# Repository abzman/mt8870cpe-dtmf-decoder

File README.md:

# mt8870cpe-dtmf-decoder

https://abzman2k.wordpress.com/2024/01/01/dtmf-decoder-board-mitel-mt8870ce/

https://abzman2k.wordpress.com/2024/03/23/dtmf-decoder-board-testing-success/

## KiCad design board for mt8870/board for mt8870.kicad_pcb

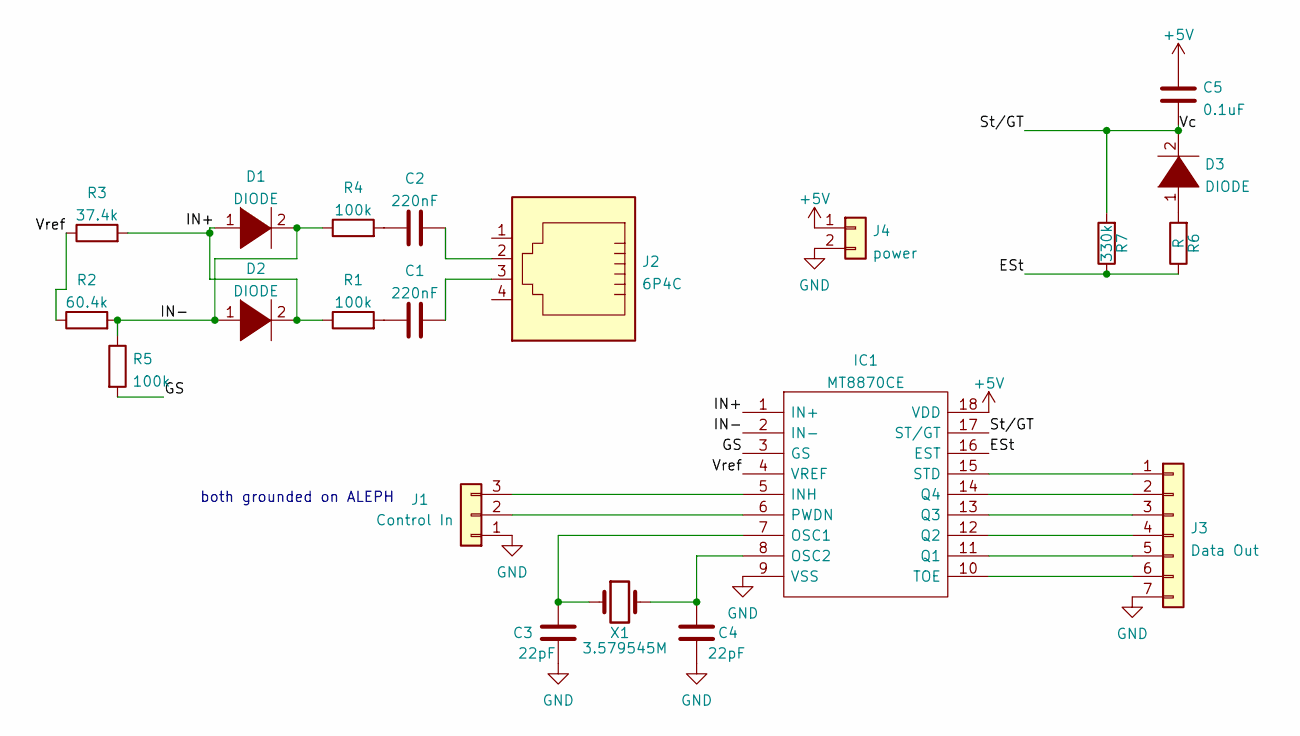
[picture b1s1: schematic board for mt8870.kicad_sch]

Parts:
C1, C2: 220nF; C_Rect_L7.0mm_W3.5mm_P5.00mm
C3, C4: 22pF; C_0603_1608Metric
C5: 0.1uF; C_0603_1608Metric
D1, D2, D3: DIODE; D_A-405_P5.08mm_Vertical_AnodeUp
IC1: MT8870CE; DIP-18_W7.62mm; Manufacturer_Part_Number MT8870CE
J1: Control In; PinHeader_1x03_P2.54mm_Vertical
J2: 6P4C; RJ14_Connfly_DS1133-S4_Horizontal
J3: Data Out; PinHeader_1x07_P2.54mm_Vertical
J4: power; PinHeader_1x02_P2.54mm_Vertical
R1, R4, R5: 100k; R_Axial_DIN0207_L6.3mm_D2.5mm_P5.08mm_Vertical
R2: 60.4k; R_Axial_DIN0207_L6.3mm_D2.5mm_P5.08mm_Vertical
R3: 37.4k; R_Axial_DIN0207_L6.3mm_D2.5mm_P5.08mm_Vertical
R6: R; R_Axial_DIN0207_L6.3mm_D2.5mm_P5.08mm_Vertical
R7: 330k; R_Axial_DIN0207_L6.3mm_D2.5mm_P5.08mm_Vertical
X1: 3.579545M; Crystal_HC49-U_Vertical

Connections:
+5V: C5.1, IC1.18 (VDD), J4.1
/ESt: IC1.16 (EST), R6.1, R7.1
/GS: IC1.3 (GS), R5.2
/IN+: D1.1 (K), D2.2 (A), IC1.1 (IN+), R1.1, R3.2
/IN-: D1.2 (A), D2.1 (K), IC1.2 (IN-), R2.2, R4.1, R5.1
/St/GT: C5.2, D3.2 (A), IC1.17 (ST/GT), R7.2
/Vref: IC1.4 (VREF), R2.1, R3.1
GND: C3.2, C4.2, IC1.9 (VSS), J1.1, J3.7, J4.2
unnamed: C1.2, J2.3
unnamed: C2.2, J2.2
unnamed: D3.1 (K), R6.2
unnamed: IC1.5 (INH), J1.3
unnamed: IC1.6 (PWDN), J1.2
unnamed: C3.1, IC1.7 (OSC1), X1.1
unnamed: C4.1, IC1.8 (OSC2), X1.2
unnamed: IC1.10 (TOE), J3.6
unnamed: IC1.11 (Q1), J3.5
unnamed: IC1.12 (Q2), J3.4
unnamed: IC1.13 (Q3), J3.3
unnamed: IC1.14 (Q4), J3.2
unnamed: IC1.15 (STD), J3.1
unnamed: C1.1, R1.2
unnamed: C2.1, R4.2

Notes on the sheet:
both grounded on ALEPH

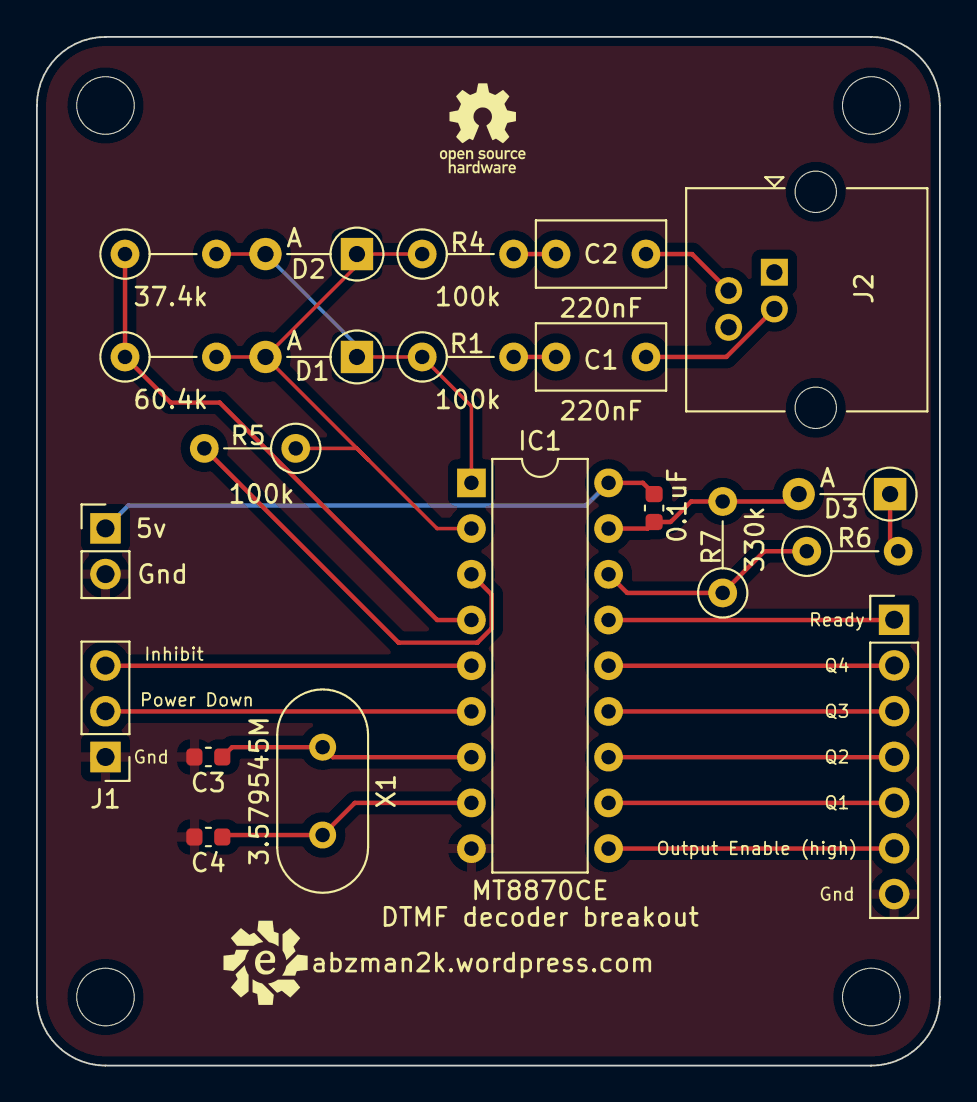
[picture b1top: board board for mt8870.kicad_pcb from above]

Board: 2 copper layers, 50.2 x 57.1 mm, 21 parts (0 on the bottom side), 23 nets.

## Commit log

2022-02-26 partial schematic from datasheet
2022-03-14 generated gerbers
2022-03-14 gerber zip
